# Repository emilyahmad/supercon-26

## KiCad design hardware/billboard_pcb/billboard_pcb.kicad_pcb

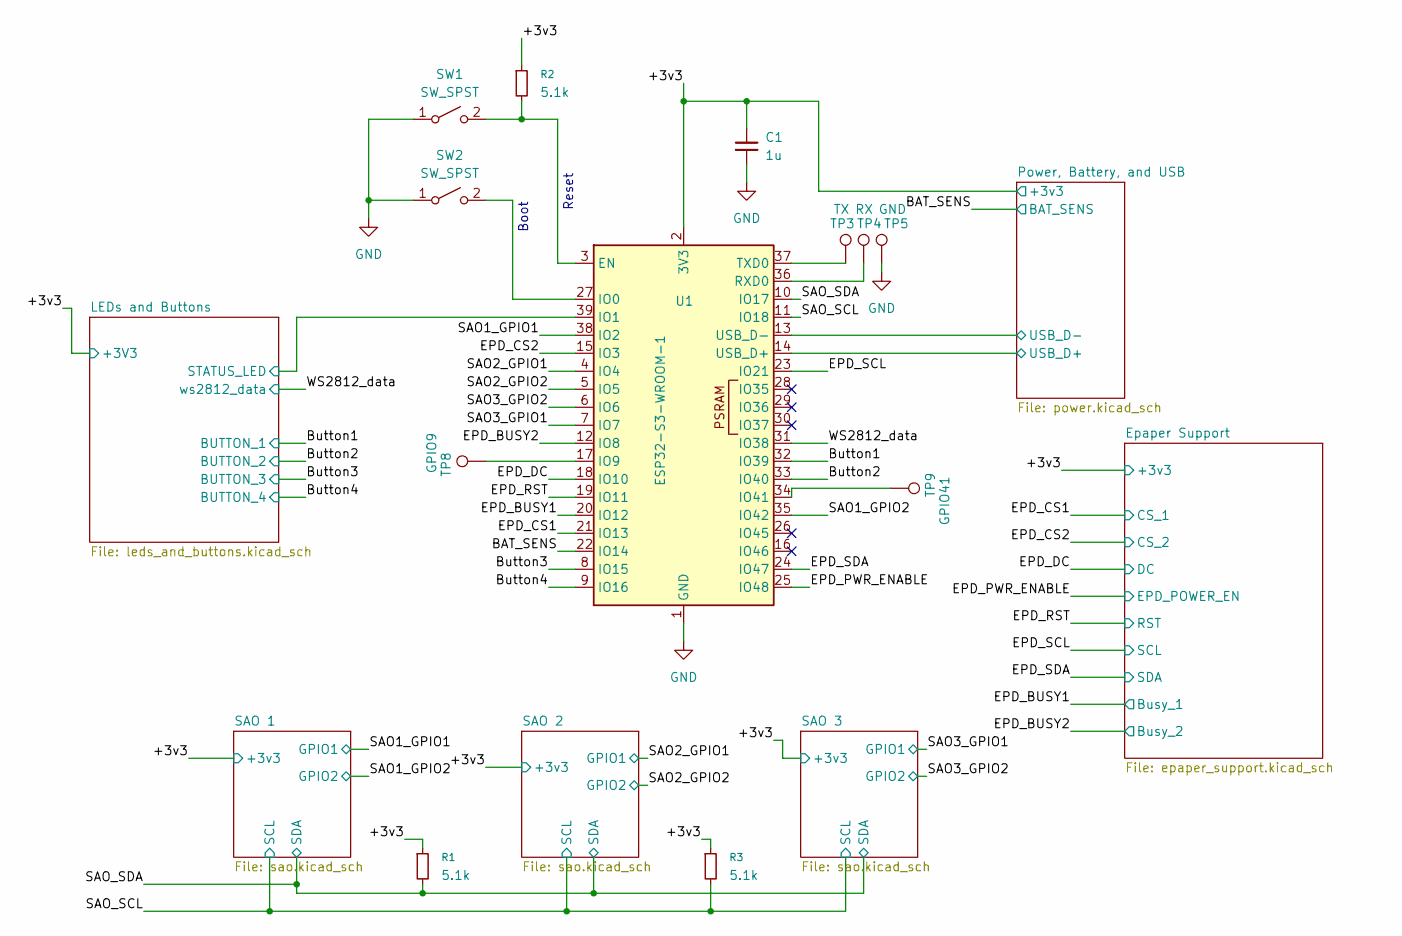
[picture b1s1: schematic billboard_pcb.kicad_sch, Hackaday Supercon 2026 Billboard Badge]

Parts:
C1: 1u; C_0603_1608Metric
R1, R2, R3: 5.1k; R_0603_1608Metric
SW1, SW2: SW_SPST; SW-SMD_L3.9-W3.0-P4.45
TP3: TX; TestPoint_Pad_1.5x1.5mm
TP4: RX; TestPoint_Pad_1.5x1.5mm
TP5: GND; TestPoint_Pad_1.5x1.5mm
TP8: GPIO9; TestPoint_Pad_1.5x1.5mm
TP9: GPIO41; TestPoint_Pad_1.5x1.5mm
U1: ESP32-S3-WROOM-1

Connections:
/+3v3: C1.1, R1.1, R2.1, R3.1, U1.2 (3V3); also elsewhere on the board
/BAT_SENS: U1.22 (IO14); also elsewhere on the board
/Button1: U1.32 (IO39); also elsewhere on the board
/Button2: U1.33 (IO40); also elsewhere on the board
/Button3: U1.8 (IO15); also elsewhere on the board
/Button4: U1.9 (IO16); also elsewhere on the board
/EPD_BUSY1: U1.20 (IO12); also elsewhere on the board
/EPD_BUSY2: U1.12 (IO8); also elsewhere on the board
/EPD_CS1: U1.21 (IO13); also elsewhere on the board
/EPD_CS2: U1.15 (IO3); also elsewhere on the board
/EPD_DC: U1.18 (IO10); also elsewhere on the board
/EPD_PWR_ENABLE: U1.25 (IO48); also elsewhere on the board
/EPD_RST: U1.19 (IO11); also elsewhere on the board
/EPD_SCL: U1.23 (IO21); also elsewhere on the board
/EPD_SDA: U1.24 (IO47); also elsewhere on the board
/LEDs and Buttons/STATUS_LED: U1.39 (IO1); also elsewhere on the board
/Power, Battery, and USB/USB_D+: U1.14 (USB_D+); also elsewhere on the board
/Power, Battery, and USB/USB_D-: U1.13 (USB_D-); also elsewhere on the board
/SAO1_GPIO1: U1.38 (IO2); also elsewhere on the board
/SAO1_GPIO2: U1.35 (IO42); also elsewhere on the board
/SAO2_GPIO1: U1.4 (IO4); also elsewhere on the board
/SAO2_GPIO2: U1.5 (IO5); also elsewhere on the board
/SAO3_GPIO1: U1.7 (IO7); also elsewhere on the board
/SAO3_GPIO2: U1.6 (IO6); also elsewhere on the board
/SAO_SCL: R3.2, U1.11 (IO18); also elsewhere on the board
/SAO_SDA: R1.2, U1.10 (IO17); also elsewhere on the board
/WS2812_data: U1.31 (IO38); also elsewhere on the board
GND: C1.2, SW1.1 (A), SW2.1 (A), TP5.1 (1_1), U1.1 (GND), U1.40 (GND), U1.41 (GND); also elsewhere on the board
unnamed: R2.2, SW1.2 (B), U1.3 (EN)
unnamed: SW2.2 (B), U1.27 (IO0)
unnamed: TP8.1 (1_1), U1.17 (IO9)
unnamed: TP9.1 (1_1), U1.34 (IO41)
unnamed: TP4.1 (1_1), U1.36 (RXD0)
unnamed: TP3.1 (1_1), U1.37 (TXD0)

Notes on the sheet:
Boot
Reset

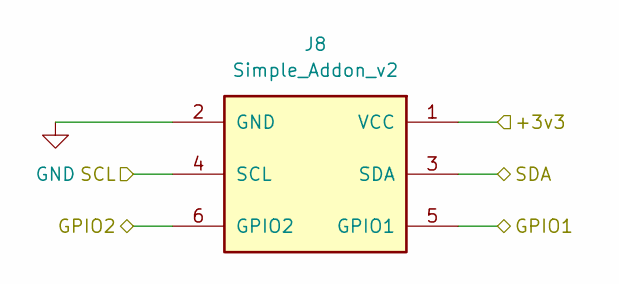
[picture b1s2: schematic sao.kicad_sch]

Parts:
J8: Simple_Addon_v2; Simple_Addon_v2-BADGE-2x3

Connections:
/+3v3: J8.1 (VCC); also elsewhere on the board
/SAO1_GPIO1: J8.5 (GPIO1); also elsewhere on the board
/SAO1_GPIO2: J8.6 (GPIO2); also elsewhere on the board
/SAO_SCL: J8.4 (SCL); also elsewhere on the board
/SAO_SDA: J8.3 (SDA); also elsewhere on the board
GND: J8.2 (GND); also elsewhere on the board

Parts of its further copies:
J9, J10: Simple_Addon_v2; Simple_Addon_v2-BADGE-2x3

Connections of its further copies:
/+3v3: J9.1 (VCC), J10.1 (VCC); also elsewhere on the board
/SAO2_GPIO1: J9.5 (GPIO1); also elsewhere on the board
/SAO2_GPIO2: J9.6 (GPIO2); also elsewhere on the board
/SAO3_GPIO1: J10.5 (GPIO1); also elsewhere on the board
/SAO3_GPIO2: J10.6 (GPIO2); also elsewhere on the board
/SAO_SCL: J9.4 (SCL), J10.4 (SCL); also elsewhere on the board
/SAO_SDA: J9.3 (SDA), J10.3 (SDA); also elsewhere on the board
GND: J9.2 (GND), J10.2 (GND); also elsewhere on the board

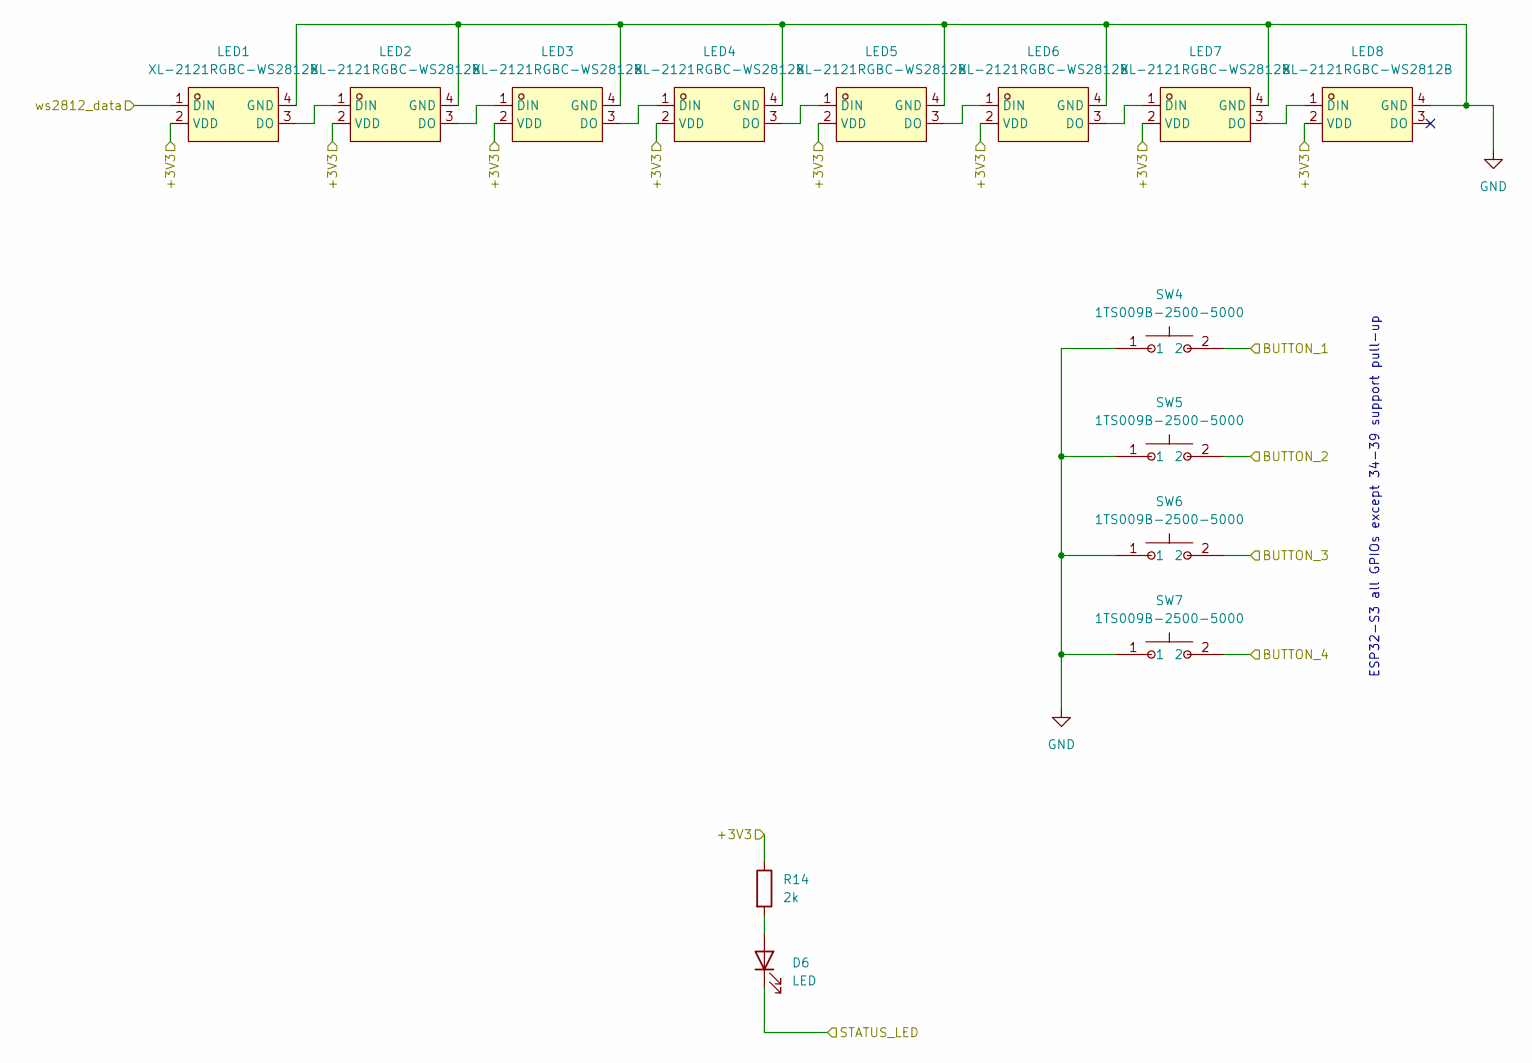
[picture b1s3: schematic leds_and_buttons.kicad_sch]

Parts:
D6: LED; LED_0603_1608Metric
LED1, LED2, LED3, LED4, LED5, LED6, LED7, LED8: XL-2121RGBC-WS2812B; LED-SMD_4P-L2.1-W2.1-BR_XL-2121RGBC-WS2812B; MPN XL-2121RGBC-2812B; LCSC Part C5349957
R14: 2k; R_0603_1608Metric
SW4, SW5, SW6, SW7: 1TS009B-2500-5000; SW-SMD_L6.0-W6.0-P6.00-LS6.6; MPN 1TS009B-2500-5000-CT; LCSC Part C255816

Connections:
/+3v3: LED1.2 (VDD), LED2.2 (VDD), LED3.2 (VDD), LED4.2 (VDD), LED5.2 (VDD), LED6.2 (VDD), LED7.2 (VDD), LED8.2 (VDD), R14.1; also elsewhere on the board
/Button1: SW4.2; also elsewhere on the board
/Button2: SW5.2; also elsewhere on the board
/Button3: SW6.2; also elsewhere on the board
/Button4: SW7.2; also elsewhere on the board
/LEDs and Buttons/STATUS_LED: D6.1 (K); also elsewhere on the board
/WS2812_data: LED1.1 (DIN); also elsewhere on the board
GND: LED1.4 (GND), LED2.4 (GND), LED3.4 (GND), LED4.4 (GND), LED5.4 (GND), LED6.4 (GND), LED7.4 (GND), LED8.4 (GND), SW4.1, SW5.1, SW6.1, SW7.1; also elsewhere on the board
unnamed: D6.2 (A), R14.2
unnamed: LED1.3 (DO), LED2.1 (DIN)
unnamed: LED2.3 (DO), LED3.1 (DIN)
unnamed: LED3.3 (DO), LED4.1 (DIN)
unnamed: LED4.3 (DO), LED5.1 (DIN)
unnamed: LED5.3 (DO), LED6.1 (DIN)
unnamed: LED6.3 (DO), LED7.1 (DIN)
unnamed: LED7.3 (DO), LED8.1 (DIN)

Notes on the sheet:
ESP32-S3 all GPIOs except 34-39 support pull-up

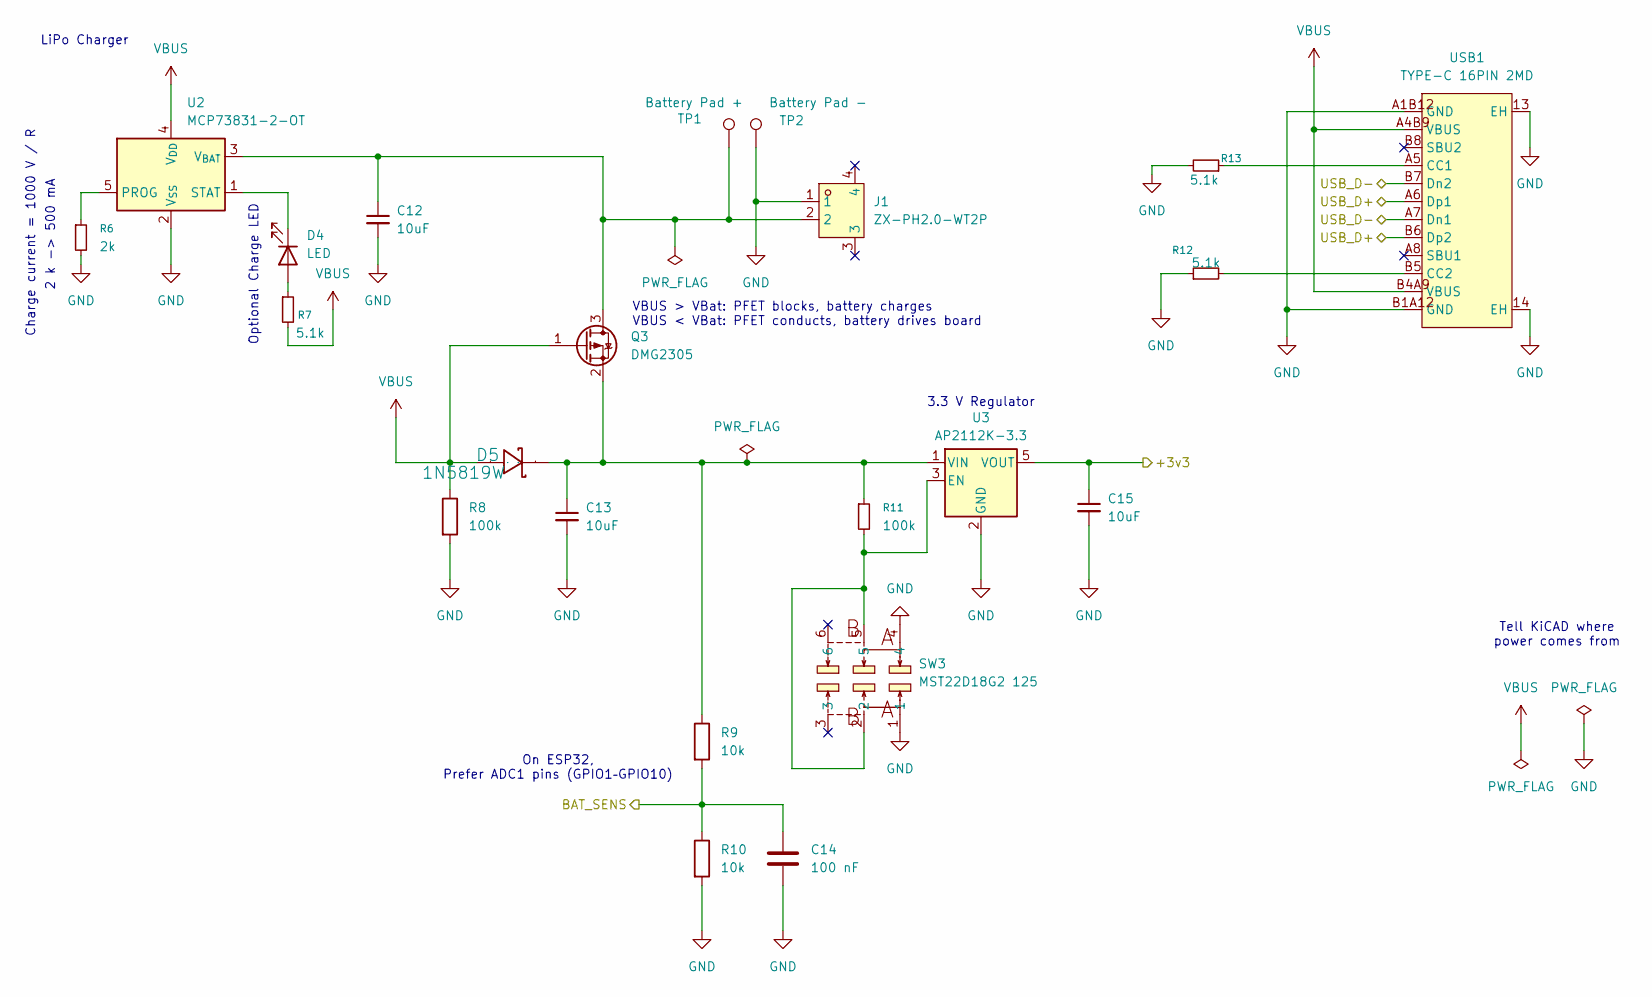
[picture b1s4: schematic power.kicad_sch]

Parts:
C12, C13, C15: 10uF; C_0603_1608Metric
C14: 100 nF; C_0603_1608Metric
D4: LED; LED_0603_1608Metric
D5: 1N5819W; SOD-123_L2.7-W1.6-LS3.7-RD; Manufacturer Part 1N5819W; LCSC Part C963381
J1: ZX-PH2.0-WT2P; CONN-SMD_ZX-PH2.0-WT2P; MPN ZX-PH2.0-WT2P; LCSC Part C7429689
Q3: DMG2305; SOT-23-3_L2.9-W1.3-P0.95-LS2.4-BR-1; LCSC Part C2940629
R6: 2k; R_0603_1608Metric
R7, R12, R13: 5.1k; R_0603_1608Metric
R8, R11: 100k; R_0603_1608Metric
R9, R10: 10k; R_0603_1608Metric
SW3: MST22D18G2 125; SW-SMD_MST22D18G2; MPN MST22D18G2 125; LCSC Part C2906280
TP1: Battery Pad +; TestPoint_Pad_3.0x3.0mm
TP2: Battery Pad -; TestPoint_Pad_3.0x3.0mm
U2: MCP73831-2-OT; SOT-23-5_L3.0-W1.7-P0.95-LS2.8-BL; LCSC Part C424093
U3: AP2112K-3.3; SOT-25-5_L2.9-W1.6-P0.95-LS2.8-BL; LCSC Part C51118
USB1: TYPE-C 16PIN 2MD; USB-C-SMD_TYPE-C-16PIN-2MD-073; MPN TYPE-C 16PIN 2MD(073); LCSC Part C2765186

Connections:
/+3v3: C15.1, U3.5 (VOUT); also elsewhere on the board
/BAT_SENS: C14.1, R9.2, R10.1; also elsewhere on the board
/Power, Battery, and USB/USB_D+: USB1.A6 (Dp1), USB1.B6 (Dp2); also elsewhere on the board
/Power, Battery, and USB/USB_D-: USB1.A7 (Dn1), USB1.B7 (Dn2); also elsewhere on the board
GND: C12.2, C13.2, C14.2, C15.2, J1.1, R6.2, R8.2, R10.2, R12.1, R13.2, SW3.1, SW3.4, TP2.1 (1_1), U2.2 (V_{SS}), U3.2 (GND), USB1.13 (EH), USB1.14 (EH), USB1.A1B12 (GND), USB1.B1A12 (GND); also elsewhere on the board
unnamed: D4.2 (A), R7.1
unnamed: D4.1 (K), U2.1 (STAT)
unnamed: C12.1, J1.2, Q3.3 (D), TP1.1 (1_1), U2.3 (V_{BAT})
unnamed: C13.1, D5.1, Q3.2 (S), R9.1, R11.1, U3.1 (VIN)
unnamed: R6.1, U2.5 (PROG)
unnamed: R11.2, SW3.2, SW3.5, U3.3 (EN)
unnamed: R13.1, USB1.A5 (CC1)
unnamed: R12.2, USB1.B5 (CC2)
VBUS: D5.2, Q3.1 (G), R7.2, R8.1, U2.4 (V_{DD}), USB1.A4B9 (VBUS), USB1.B4A9 (VBUS)

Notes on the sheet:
3.3 V Regulator
Optional Charge LED
On ESP32, Prefer ADC1 pins (GPIO1–GPIO10)
VBUS > VBat: PFET blocks, battery charges VBUS < VBat: PFET conducts, battery drives board
LiPo Charger
2 k -> 500 mA
Tell KiCAD where power comes from
Charge current = 1000 V / R

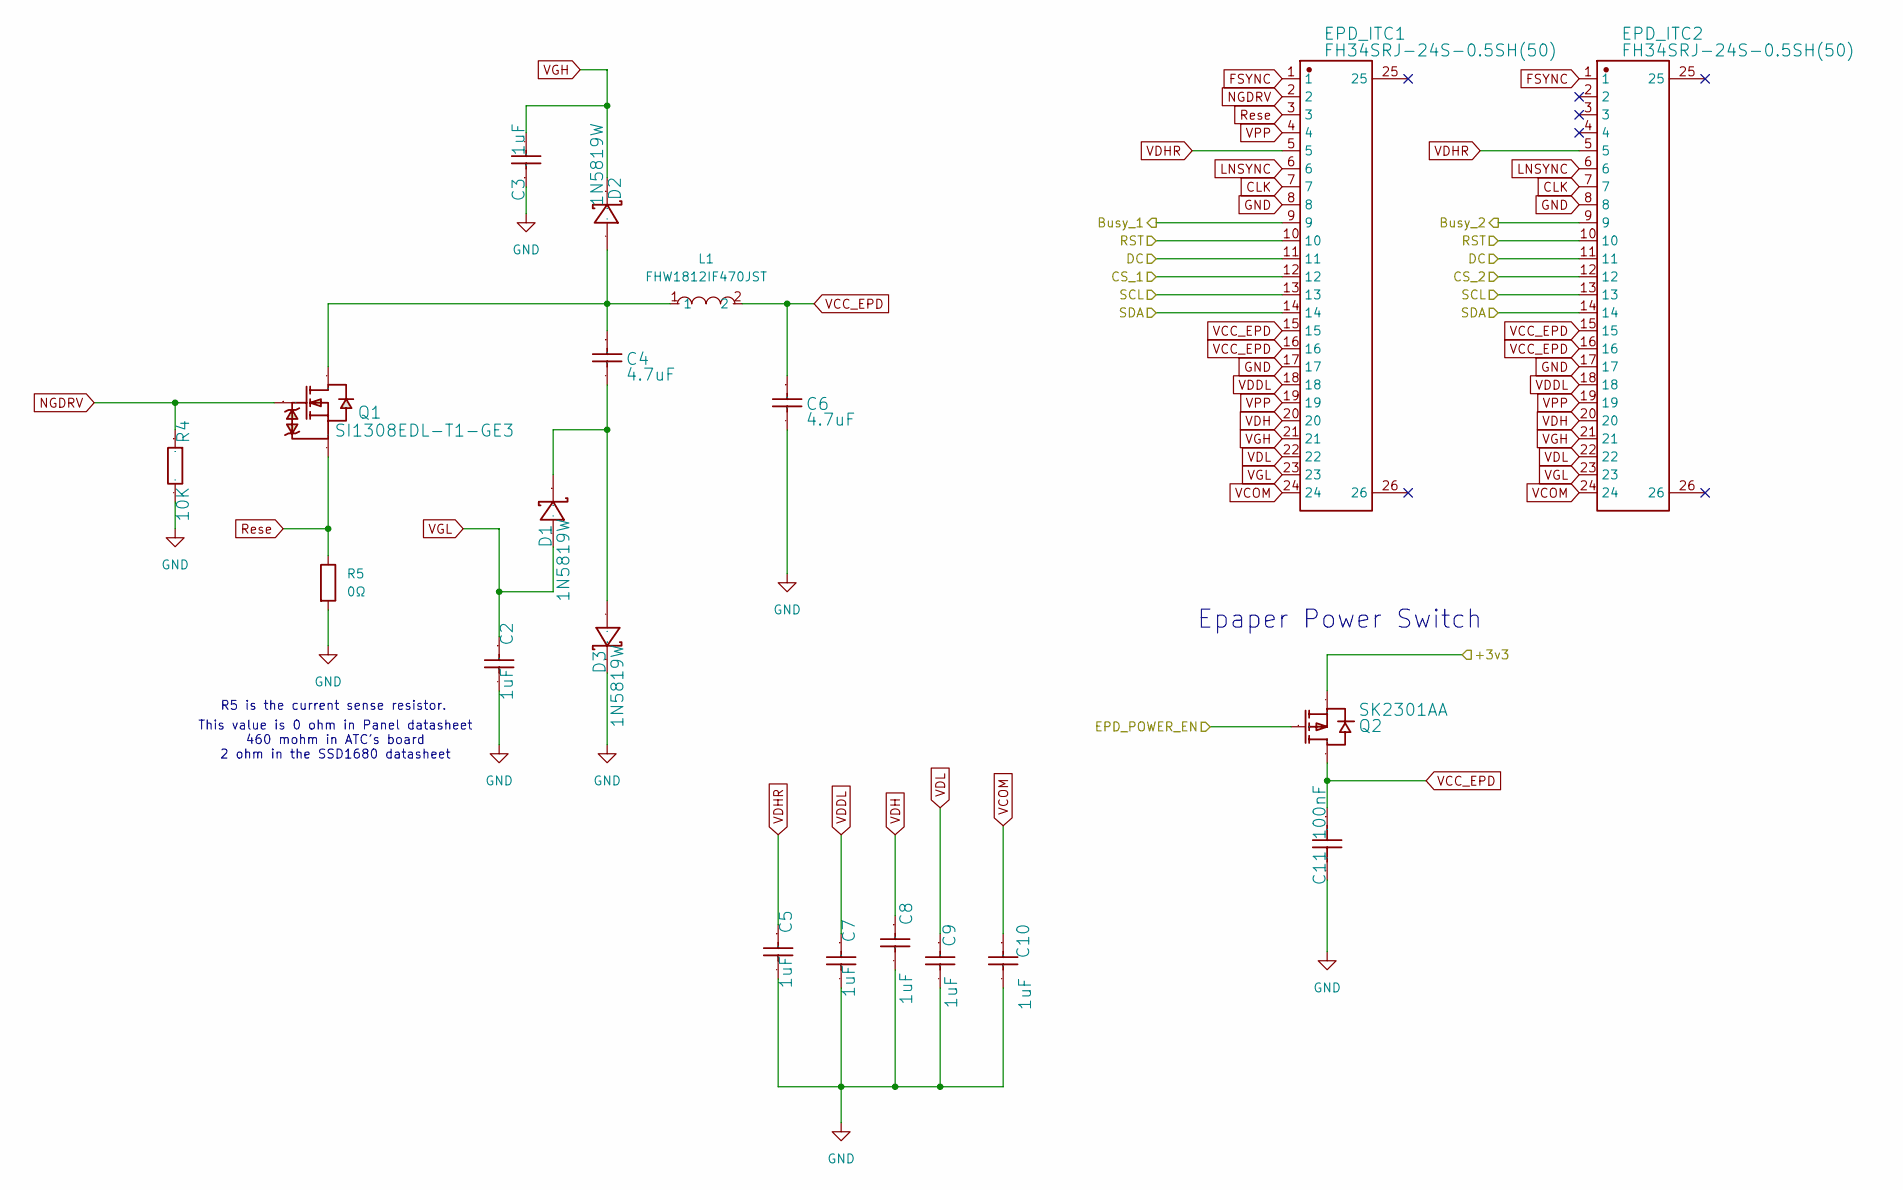
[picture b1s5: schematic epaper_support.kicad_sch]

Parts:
C2, C3, C5, C7, C8, C9, C10: 1uF; C_0603_1608Metric; Manufacturer Part CL10A105KO8NNNC
C4, C6: 4.7uF; C_0603_1608Metric; Manufacturer Part CL10A475KO8NNNC
C11: 100nF; C_0603_1608Metric; Manufacturer Part TCC0603X7R104K500CT
D1, D2, D3: 1N5819W; SOD-123_L2.7-W1.6-LS3.7-RD; Manufacturer Part 1N5819W; LCSC Part C963381
EPD_ITC1, EPD_ITC2: FH34SRJ-24S-0.5SH(50); FFC-SMD_24P-P0.50_FH34SRJ-24S-0.5SH; Manufacturer Part FH34SRJ-24S-0.5SH(50); LCSC Part C324726
L1: FHW1812IF470JST; IND-SMD_L4.8-W3.4; MPN FHW1812IF470JST; LCSC Part C394129
Q1: SI1308EDL-T1-GE3; SOT-323_L2.0-W1.3-P1.30-LS2.1-BR; Manufacturer Part SI1308EDL-T1-GE3; LCSC Part C469327
Q2: SK2301AA; SOT-23-3_L2.9-W1.6-P1.90-LS2.8-BR; Manufacturer Part SK2301AA1SHB; LCSC Part C118316
R4: 10K; R_0603_1608Metric; Manufacturer Part RS-03K103JT
R5: 0Ω; R_0603_1608Metric

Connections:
/+3v3: Q2.2 (S); also elsewhere on the board
/EPD_BUSY1: EPD_ITC1.9; also elsewhere on the board
/EPD_BUSY2: EPD_ITC2.9; also elsewhere on the board
/EPD_CS1: EPD_ITC1.12; also elsewhere on the board
/EPD_CS2: EPD_ITC2.12; also elsewhere on the board
/EPD_DC: EPD_ITC1.11, EPD_ITC2.11; also elsewhere on the board
/EPD_PWR_ENABLE: Q2.1 (G); also elsewhere on the board
/EPD_RST: EPD_ITC1.10, EPD_ITC2.10; also elsewhere on the board
/EPD_SCL: EPD_ITC1.13, EPD_ITC2.13; also elsewhere on the board
/EPD_SDA: EPD_ITC1.14, EPD_ITC2.14; also elsewhere on the board
CLK: EPD_ITC1.7, EPD_ITC2.7
FSYNC: EPD_ITC1.1, EPD_ITC2.1
GND: C2.2, C3.1, C5.2, C6.2, C7.2, C8.2, C9.2, C10.2, C11.2, D3.1, EPD_ITC1.8, EPD_ITC1.17, EPD_ITC2.8, EPD_ITC2.17, R4.2, R5.2; also elsewhere on the board
LNSYNC: EPD_ITC1.6, EPD_ITC2.6
NGDRV: EPD_ITC1.2, Q1.1 (G), R4.1
unnamed: C4.2, D1.1, D3.2
unnamed: C4.1, D2.2, L1.1, Q1.3 (D)
Rese: EPD_ITC1.3, Q1.2 (S), R5.1
VCC_EPD: C6.1, C11.1, EPD_ITC1.15, EPD_ITC1.16, EPD_ITC2.15, EPD_ITC2.16, L1.2, Q2.3 (D)
VCOM: C10.1, EPD_ITC1.24, EPD_ITC2.24
VDDL: C7.1, EPD_ITC1.18, EPD_ITC2.18
VDH: C8.1, EPD_ITC1.20, EPD_ITC2.20
VDHR: C5.1, EPD_ITC1.5, EPD_ITC2.5
VDL: C9.1, EPD_ITC1.22, EPD_ITC2.22
VGH: C3.2, D2.1, EPD_ITC1.21, EPD_ITC2.21
VGL: C2.1, D1.2, EPD_ITC1.23, EPD_ITC2.23
VPP: EPD_ITC1.4, EPD_ITC1.19, EPD_ITC2.19

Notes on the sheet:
R5 is the current sense resistor.
Epaper Power Switch
This value is 0 ohm in Panel datasheet 460 mohm in ATC's board 2 ohm in the SSD1680 datasheet

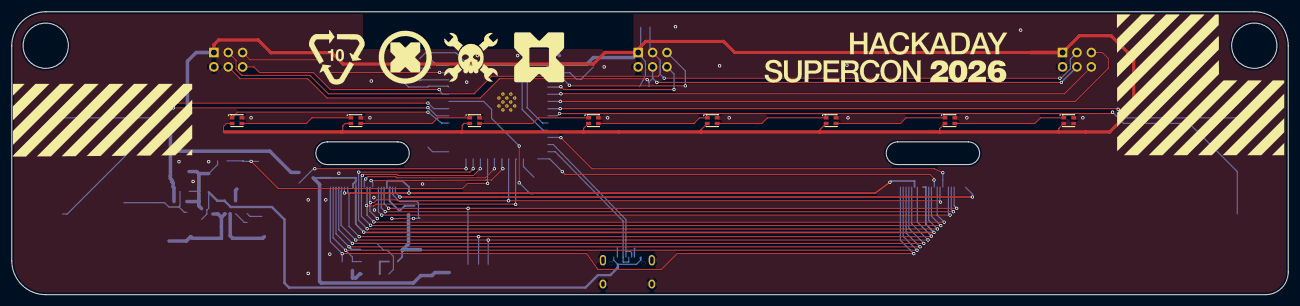
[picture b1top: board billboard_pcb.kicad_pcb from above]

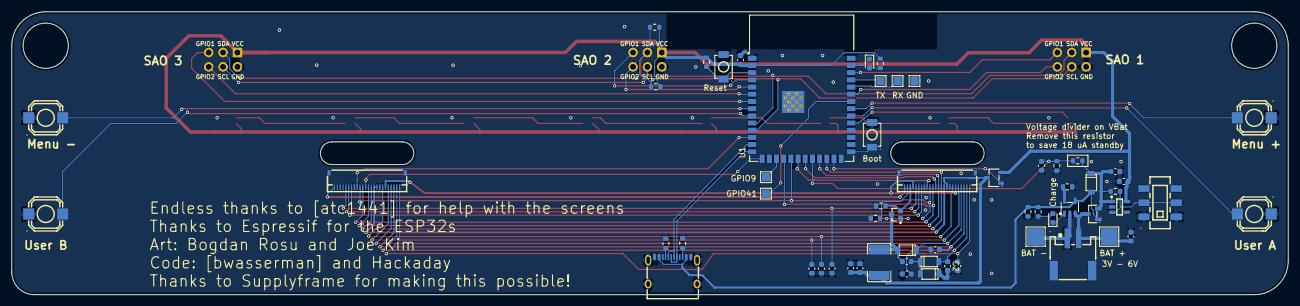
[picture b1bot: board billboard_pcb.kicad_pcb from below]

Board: 2 copper layers, 225.6 x 50.0 mm, 71 parts (60 on the bottom side), 67 nets.

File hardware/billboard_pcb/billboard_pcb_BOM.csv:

Reference,Qty,Value,Footprint,Datasheet,Manufacturer Part,Supplier,Supplier Part,Manufacturer,Description
C1,1,1u,Capacitor_SMD:C_0603_1608Metric,,,LCSC,C1592,,"Unpolarized capacitor, small symbol"
"C2,C3,C5,C7,C8,C9,C10",7,1uF,Capacitor_SMD:C_0603_1608Metric,,CL10A105KO8NNNC,LCSC,C1592,SAMSUNG,
"C4,C6",2,4.7uF,Capacitor_SMD:C_0603_1608Metric,,CL10A475KO8NNNC,LCSC,C19666,SAMSUNG,
C11,1,100nF,Capacitor_SMD:C_0603_1608Metric,,TCC0603X7R104K500CT,LCSC,C282519,CCTC,
"C12,C13,C15",3,10uF,Capacitor_SMD:C_0603_1608Metric,,,,,,"Unpolarized capacitor, small symbol"
C14,1,100 nF,Capacitor_SMD:C_0603_1608Metric,,,,,,Unpolarized capacitor
"D1,D2,D3,D5",4,1N5819W,easyeda2kicad_fp:SOD-123_L2.7-W1.6-LS3.7-RD,,1N5819W,LCSC,C169540,Shandong Jingdao Microelectronics,
"D4,  D6",2,LED,LED_SMD:LED_0603_1608Metric,,,LCSC,C2290,,"Light emitting diode,  0603, yellow"
"EPD_ITC1,EPD_ITC2",2,FH34SRJ-24S-0.5SH(50),easyeda2kicad_fp:FFC-SMD_24P-P0.50_FH34SRJ-24S-0.5SH,,FH34SRJ-24S-0.5SH(50),LCSC,C2919499,Hirose,
J1,1,ZX-PH2.0-WT2P,easyeda2kicad_fp:CONN-SMD_ZX-PH2.0-WT2P,https://www.lcsc.com/datasheet/C7429689.pdf,,LCSC,C7429689,Megastar(兆星),
"J8,J9,J10",3,Simple_Addon_v2,Simple_Addon_v2:Simple_Addon_v2-BADGE-2x3,https://hackaday.io/project/175182-simple-add-ons-sao,,LCSC,C2897404,,
L1,1,FHW1812IF470JST,easyeda2kicad_fp:IND-SMD_L4.8-W3.4,https://lcsc.com/product-detail/HF-Inductors_Guangdong-Fengh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,,LCSC,C394129,FH(风华),
"LED1,LED2,LED3,LED4,LED5,LED6,LED7,LED8",8,XL-2121RGBC-WS2812B,easyeda2kicad_fp:LED-SMD_4P-L2.1-W2.1-BR_XL-2121RGBC-WS2812B,https://www.lcsc.com/datasheet/C5349957.pdf,,LCSC,C5349957,XINGLIGHT(成兴光),
Q1,1,SI1308EDL-T1-GE3,easyeda2kicad_fp:SOT-323_L2.0-W1.3-P1.30-LS2.1-BR,,SI1308EDL-T1-GE3,LCSC,C469327,VISHAY(威世),
Q2,1,SK2301AA,easyeda2kicad_fp:SOT-23-3_L2.9-W1.6-P1.90-LS2.8-BR,,SK2301AA1SHB,LCSC,C118153,SHIKUES(时科),
Q3,1,DMG2305,easyeda2kicad_fp:SOT-23-3_L2.9-W1.3-P0.95-LS2.4-BR-1,https://www.diodes.com/assets/Datasheets/DMG2301L.pdf,,LCSC,C5261054,,"-3A Id, -20V Vds, P-Channel MOSFET, SOT-23"
"R1,R3",2,R_Small,Resistor_SMD:R_0603_1608Metric,,,,,,"Resistor, small symbol"
"R2,R7,R12,R13",4,5.1k,Resistor_SMD:R_0603_1608Metric,,,,,,"Resistor, small symbol"
R4,1,10K,Resistor_SMD:R_0603_1608Metric,,RS-03K103JT,LCSC,C73809,FH,
R5,1,0Ω,Resistor_SMD:R_0603_1608Metric,,,,,,Resistor
R6,1,2k,Resistor_SMD:R_0603_1608Metric,,,,,,"Resistor, small symbol"
"R8,R11",2,100k,Resistor_SMD:R_0603_1608Metric,,,,,,"Resistor,Resistor, small symbol"
"R9,R10",2,10k,Resistor_SMD:R_0603_1608Metric,,,,,,Resistor
R14,1,R,Resistor_SMD:R_0603_1608Metric,,,,,,Resistor
"SW1,SW2",2,SW_SPST,easyeda2kicad_fp:SW-SMD_L3.9-W3.0-P4.45,,,LCSC,C720477,XUNPU(讯普),Single Pole Single Throw (SPST) switch
SW3,1,MST22D18G2 125,easyeda2kicad_fp:SW-SMD_MST22D18G2,https://www.lcsc.com/datasheet/C2906280.pdf,,LCSC,C2906280,SHOU HAN(首韩),
"SW4,SW5,SW6,SW7",4,1TS009B-2500-5000,easyeda2kicad_fp:SW-SMD_L6.0-W6.0-P6.00-LS6.6,https://lcsc.com/product-detail/Others_HYP-1TS009B-2500-5000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,,LCSC,C255816,HYP(鸿源精密),
TP1,1,Battery Pad +,TestPoint:TestPoint_Pad_3.0x3.0mm,,,,,,test point
TP2,1,Battery Pad -,TestPoint:TestPoint_Pad_3.0x3.0mm,,,,,,test point
TP3,1,TX,TestPoint:TestPoint_Pad_1.5x1.5mm,,,,,,test point
TP4,1,RX,TestPoint:TestPoint_Pad_1.5x1.5mm,,,,,,test point
TP5,1,GND,TestPoint:TestPoint_Pad_1.5x1.5mm,,,,,,test point
TP6,1,GPIO17,TestPoint:TestPoint_Pad_1.5x1.5mm,,,,,,test point
TP7,1,GPIO18,TestPoint:TestPoint_Pad_1.5x1.5mm,,,,,,test point
TP8,1,GPIO9,TestPoint:TestPoint_Pad_1.5x1.5mm,,,,,,test point
TP9,1,GPIO41,TestPoint:TestPoint_Pad_1.5x1.5mm,,,,,,test point
U1,1,ESP32-S3-WROOM-1,RF_Module:ESP32-S3-WROOM-1,https://www.espressif.com/sites/default/files/documentation/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,,LCSC,C2913202,,"RF Module, ESP32-S3 SoC, Wi-Fi 802.11b/g/n, Bluetooth, BLE, 32-bit, 3.3V, onboard antenna, SMD"
U2,1,MCP73831-2-OT,Package_TO_SOT_SMD:SOT-23-5,http://ww1.microchip.com/downloads/en/DeviceDoc/20001984g.pdf,,LCSC,C424093,,"Single cell, Li-Ion/Li-Po charge management controller, 4.20V, Tri-State Status Output, in SOT23-5 package"
U3,1,AP2112K-3.3,Package_TO_SOT_SMD:SOT-23-5,https://www.diodes.com/assets/Datasheets/AP2112.pdf,,LCSC,C51118,,"600mA low dropout linear regulator, with enable pin, 3.8V-6V input voltage range, 3.3V fixed positive output, SOT-23-5"
USB1,1,TYPE-C 16PIN 2MD,easyeda2kicad_fp:USB-C-SMD_TYPE-C-16PIN-2MD-073,https://www.lcsc.com/datasheet/C2765186.pdf,,LCSC,C2765186,SHOU HAN(首韩),
